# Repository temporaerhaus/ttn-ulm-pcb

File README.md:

# Münsterplatine – a pcb for LoRaWan

(Münsterplatine ist german for minster pcb.)

Welcome to the TTN Ulm Münsterplatine repository.
Our local TTN-community was under the impression that there is a tremendous need for a cheap and easy to use LoRaWan All-in-one kit, and so we created one.
The work is build around the ready-made arduino Pro Mini which can be bought from various sources for under 3 EUR per piece and the RFM96W LoRa tranceiver for communication.

After the board has been designed by the members of the community, we were sponsored by Initiative Ulm Digital that funded our initial production. 
Minsternode has then been prominently featured in many events, including the yearly conference of Initiave Ulm Digital and the event "Ulm Macht Zukunft".

# 2nd major version

(The most recent revision of this variant is v1.1)

In this version we added a multitude of goodies for you comfort as a LoRaWan-enthusiast. 
The features include:
* onboard FTDI and USB, so you can flash your Arduino easily by connecting it to your PC directly
* battery connector
* _battery charger_ included, so you can charge your LiPo-battery while plugged into the PC
* a combinded wire/ufl/sma connector is also onboard.
	
# 1st major version

This version aimed to satisfy you basic LoRaWan needs in form of a pcb on which the Arduino Pro Mini and the RMF95W-module can be soldered together. 
But beware: You still need a FTDI USB<->Serial converter to flash your Arduino. 
Since there is no additional hardware, this version is less energy-hungry than Version 2

You can find this version in the [legacy branch](https://github.com/verschwoerhaus/ttn-ulm-pcb/tree/legacy).

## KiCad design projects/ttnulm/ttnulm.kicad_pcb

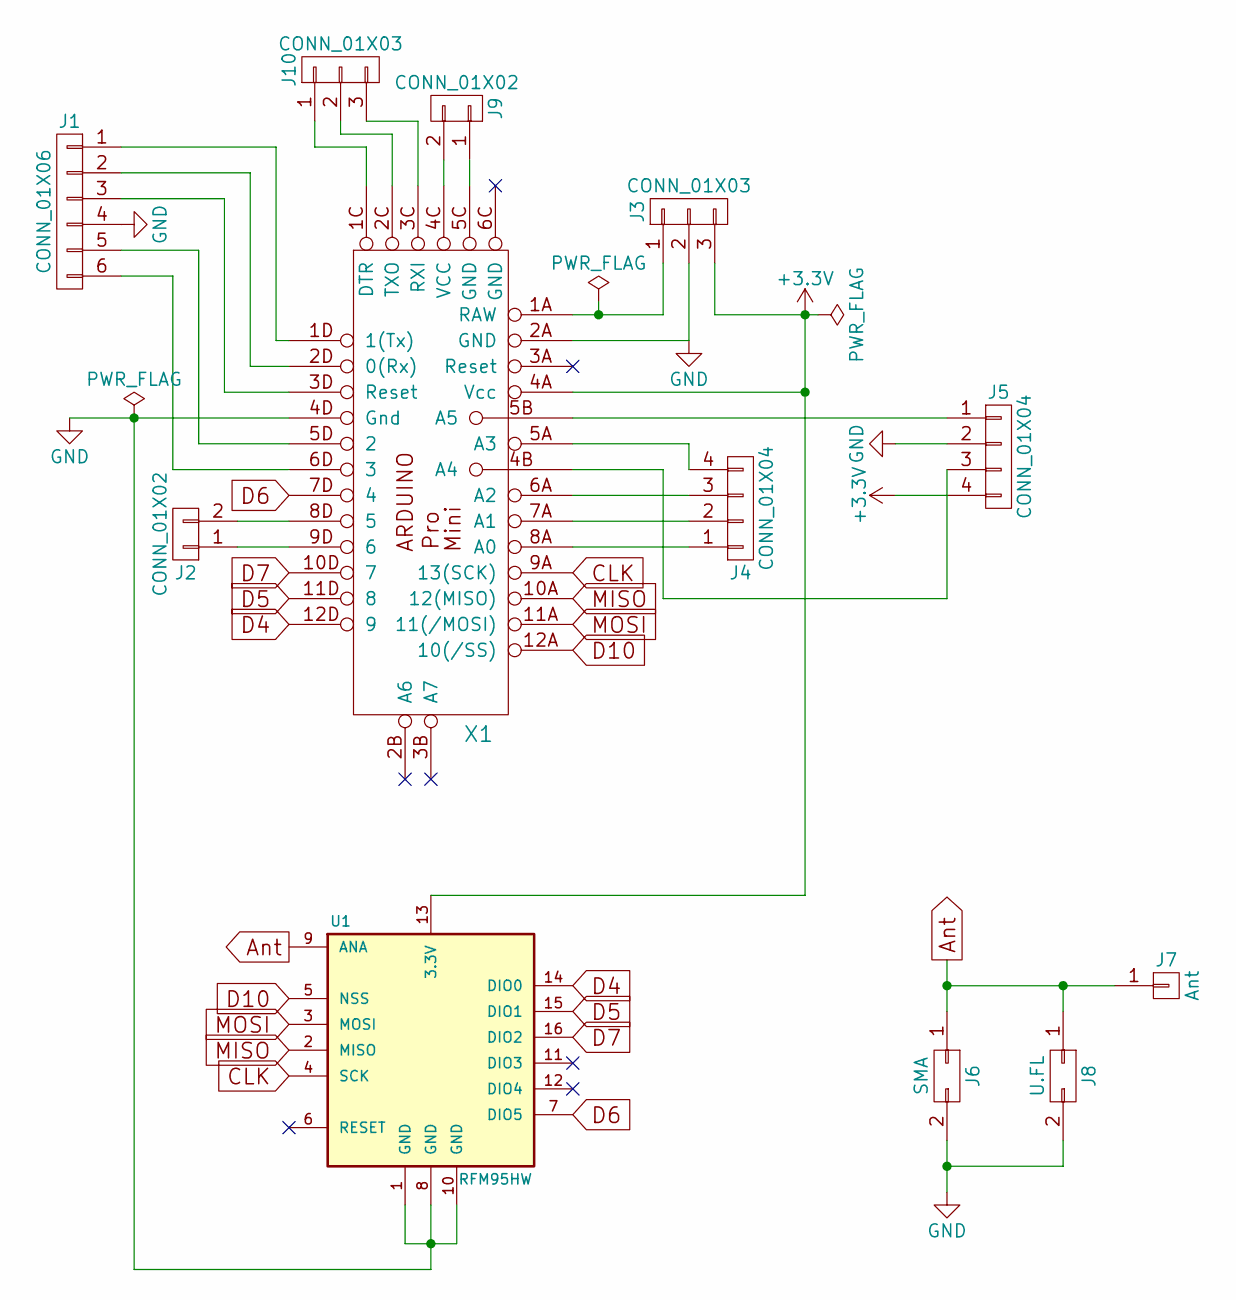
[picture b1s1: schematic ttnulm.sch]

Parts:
J1: CONN_01X06; Pin_Header_Straight_1x06_Pitch1.27mm
J2: CONN_01X02; Pin_Header_Straight_1x02_Pitch1.27mm
J3: CONN_01X03; PINHEAD1-3
J4, J5: CONN_01X04; Pin_Header_Straight_1x04_Pitch1.27mm
J6: SMA; SMA_EDGE
J7: Ant; Pin_Header_Straight_1x01_Pitch1.27mm
J8: U.FL; U.FL-COAX
J9: CONN_01X02; JST_PH_B2B-PH-SM4-TB_02x2.00mm_Straight
J10: CONN_01X03; Pin_Header_Straight_1x03_Pitch2.54mm
U1: RFM95HW; RFM69HW_SMD_ThroughHole_Handsoldering
X1: Arduino ProMini; Arduino_Pro_Mini_edited

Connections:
+3V3: J3.3, J5.4, U1.13 (3.3V), X1.4A (Vcc)
Ant: J6.1, J7.1, J8.1, U1.9 (ANA)
CLK: U1.4 (SCK), X1.9A (13(SCK))
D4: U1.14 (DIO0), X1.12D (9)
D5: U1.15 (DIO1), X1.11D (8)
D6: U1.7 (DIO5), X1.7D (4)
D7: U1.16 (DIO2), X1.10D (7)
D10: U1.5 (NSS), X1.12A (10(/SS))
GND: J1.4, J3.2, J5.2, J6.2, J8.2, J8.3, U1.1 (GND), U1.8 (GND), U1.10 (GND), X1.2A (GND), X1.4D (Gnd), X1.6C (GND)
MISO: U1.2 (MISO), X1.10A (12(MISO))
MOSI: U1.3 (MOSI), X1.11A (11(/MOSI))
unnamed: J1.1, X1.1D (1(Tx))
unnamed: J1.2, X1.2D (0(Rx))
unnamed: J1.3, X1.3D (Reset)
unnamed: J1.5, X1.5D (2)
unnamed: J1.6, X1.6D (3)
unnamed: J2.1, X1.9D (6)
unnamed: J2.2, X1.8D (5)
unnamed: J3.1, X1.1A (RAW)
unnamed: J4.1, X1.8A (A0)
unnamed: J4.2, X1.7A (A1)
unnamed: J4.3, X1.6A (A2)
unnamed: J4.4, X1.5A (A3)
unnamed: J5.1, X1.5B (A5)
unnamed: J5.3, X1.4B (A4)
unnamed: J9.1, X1.5C (GND)
unnamed: J9.2, X1.4C (VCC)
unnamed: J10.1, X1.1C (DTR)
unnamed: J10.2, X1.2C (TXO)
unnamed: J10.3, X1.3C (RXI)

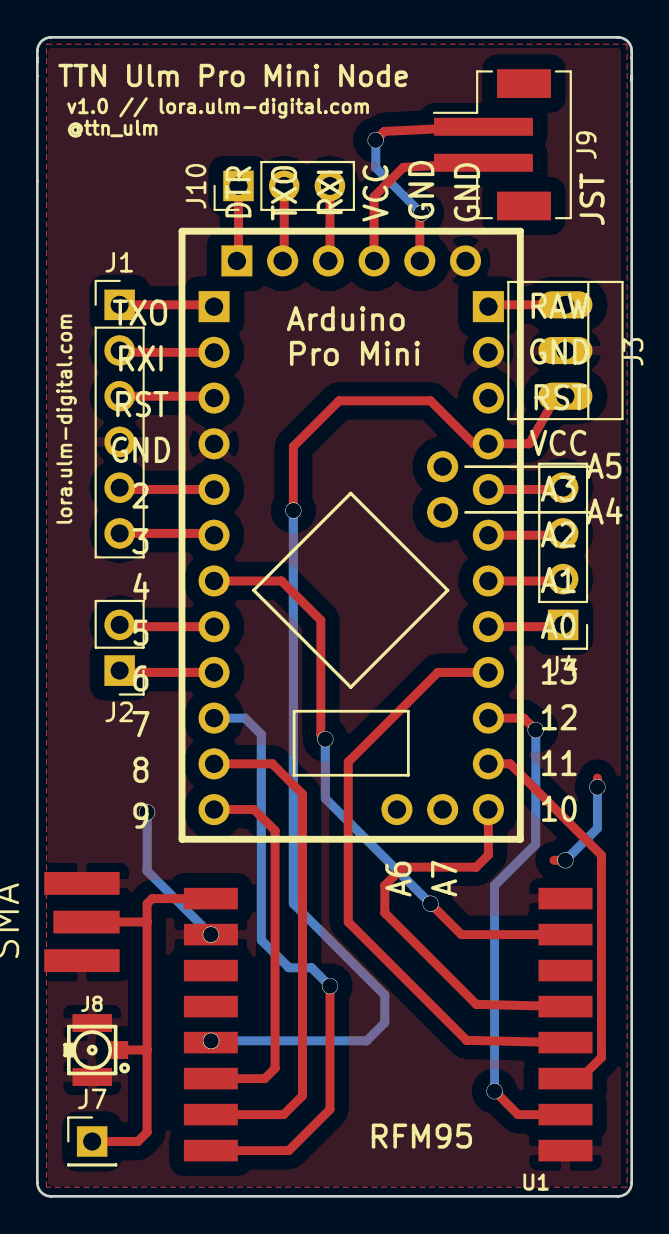
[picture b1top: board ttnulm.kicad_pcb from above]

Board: 2 copper layers, 33.0 x 64.4 mm, 11 parts (0 on the bottom side), 28 nets.

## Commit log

2017-07-06 initital commit
2017-07-11 Version 2 hinzugefügt. Todo: * Add Voltage Regulator (wire up) * Add other ProMini-Designs * Credits
2017-07-11 connected \!DTR Pin to RST
2017-07-13 reworked layout. Added voltage controller and discharging mechanism
2017-07-13 prinzipiell Produktionsreif. Todo: Verkürzen
2017-07-13 Technische Arbeiten abgeschlossen. Logo fehlt noch
2017-07-13 refactored file structure, updated README
2017-07-13 rerouted rmf power suppyl
2017-07-13 rerouted arduino power suppyl
2017-07-13 nicing of batterycharger
2017-07-15 Create LICENSE
2017-07-15 add calculations fpr v2
2017-07-15 banished macs .DS_STORE files... grml
2017-07-16 WIP: reducing height. Antenna must be refitted
2017-07-16 Board now approx 5x4 cm
2017-07-16 Successful designrule check
2017-07-16 corrected gnd path to FT232RL
2017-07-16 corrected one polygon. made antenna trace shorter
2017-07-20 replaced some parts with their bigger equivalent
2017-07-20 updated calc sheets with arduino pro mini 328p. Kudos to Simon Fuchs
2017-07-31 richtiges Arduino Pro Mini Pinout hinzugefügt
2017-07-31 nicing of some traces
2017-08-03 Added images with Ulmer Münster Solhouette.
2017-08-03 rerouted traces to make room for the big M ( =muenster)
2017-08-03 reduced colors to 2 in UlmerMünsterSilhouette.bmp
2017-08-03 #+-%&$§%&T$ picture editing.
2017-08-03 added picture of board layout
2017-08-03 Revert "added picture of board layout"
    This reverts commit 6c2dd7b23edb37982c4fb7cb2418e2451a8ef545.
2017-08-03 added new board layout
2017-08-20 Deployed Münsterdesign
2017-08-21 replaced some of the 0603 Resistors with 0805
2017-08-22 Added remaining Logos on backside silkscreen
2017-08-22 corrected one DRC-Error
2017-08-23 moved logos slightly. Tried correcting muenster's imbalance
2017-08-23 Finalized design
2017-08-23 Cam-processed
2017-08-23 added order information
2017-08-23 updated order list
2017-08-23 Last time: updated Orderlist
2017-08-23 added panelized gerber files
2017-08-23 panelized
2017-08-24 Create AUTHORS
2017-09-08 added v3 of backplate logos
2017-09-13 Fixed Bug regarding Pinout of RFM95W
2017-09-13 Added new back panel logos
2017-09-13 corrected DRC-Errors. ToDo: Right USB Slot, Diode vs. Jumper
2017-09-13 Final Final
2017-09-13 Gerber Files v2
2017-09-14 added new panelized gerber files
2017-09-14 Fixed Cap. Values for better voltage stabilazation
2017-09-22 added microUSB
2017-09-24 Added Cam-Job. Gerber Gerber Gerber
2018-01-31 Updated Design. Fixed last bugs. Updated BOM
2018-01-31 Updated BOM
2018-02-19 Added clean
2018-06-13 added battery voltage monitoring
2018-08-31 Generated Gerber-files for enhanced pcb-layout
2018-10-28 Refactored directory structure. Added some screenshots for the sake of docu
2018-10-28 Added example code; added first draft of QA code.
2021-04-15 Added some details to the history of the project
